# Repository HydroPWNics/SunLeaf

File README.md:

# SunLeaf
SunLeaf is a WiFi based remote sensor module, interfaces with I2C and UART sensors, pushes directly to the cloud.

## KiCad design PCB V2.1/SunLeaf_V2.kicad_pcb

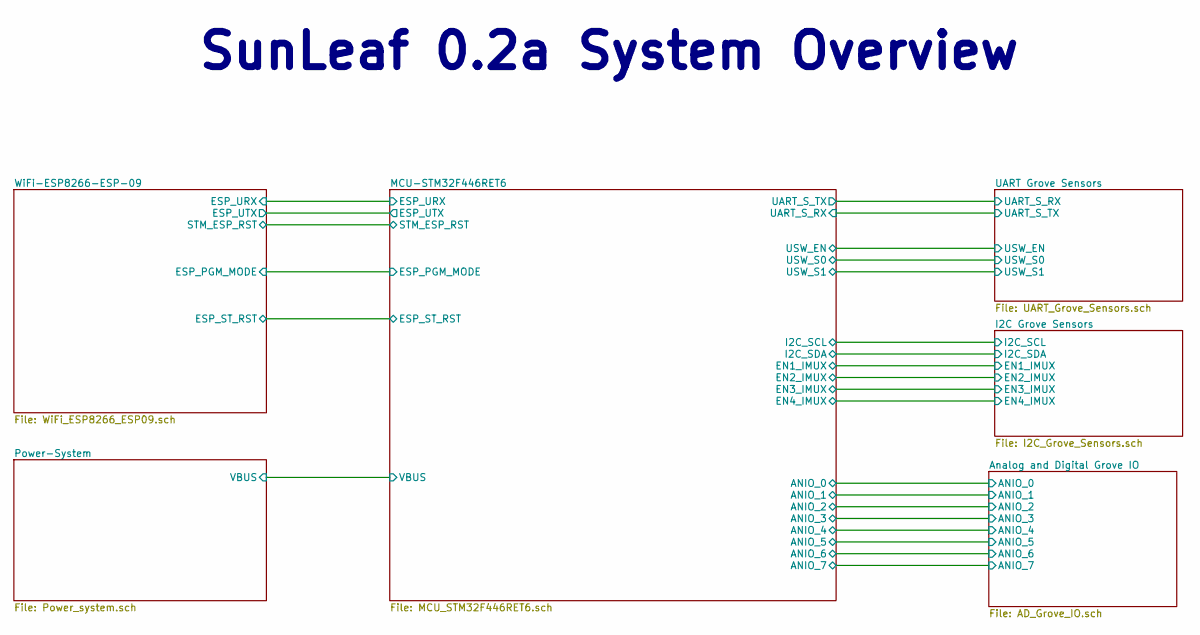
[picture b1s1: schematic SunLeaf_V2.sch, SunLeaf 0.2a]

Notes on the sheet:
SunLeaf 0.2a System Overview

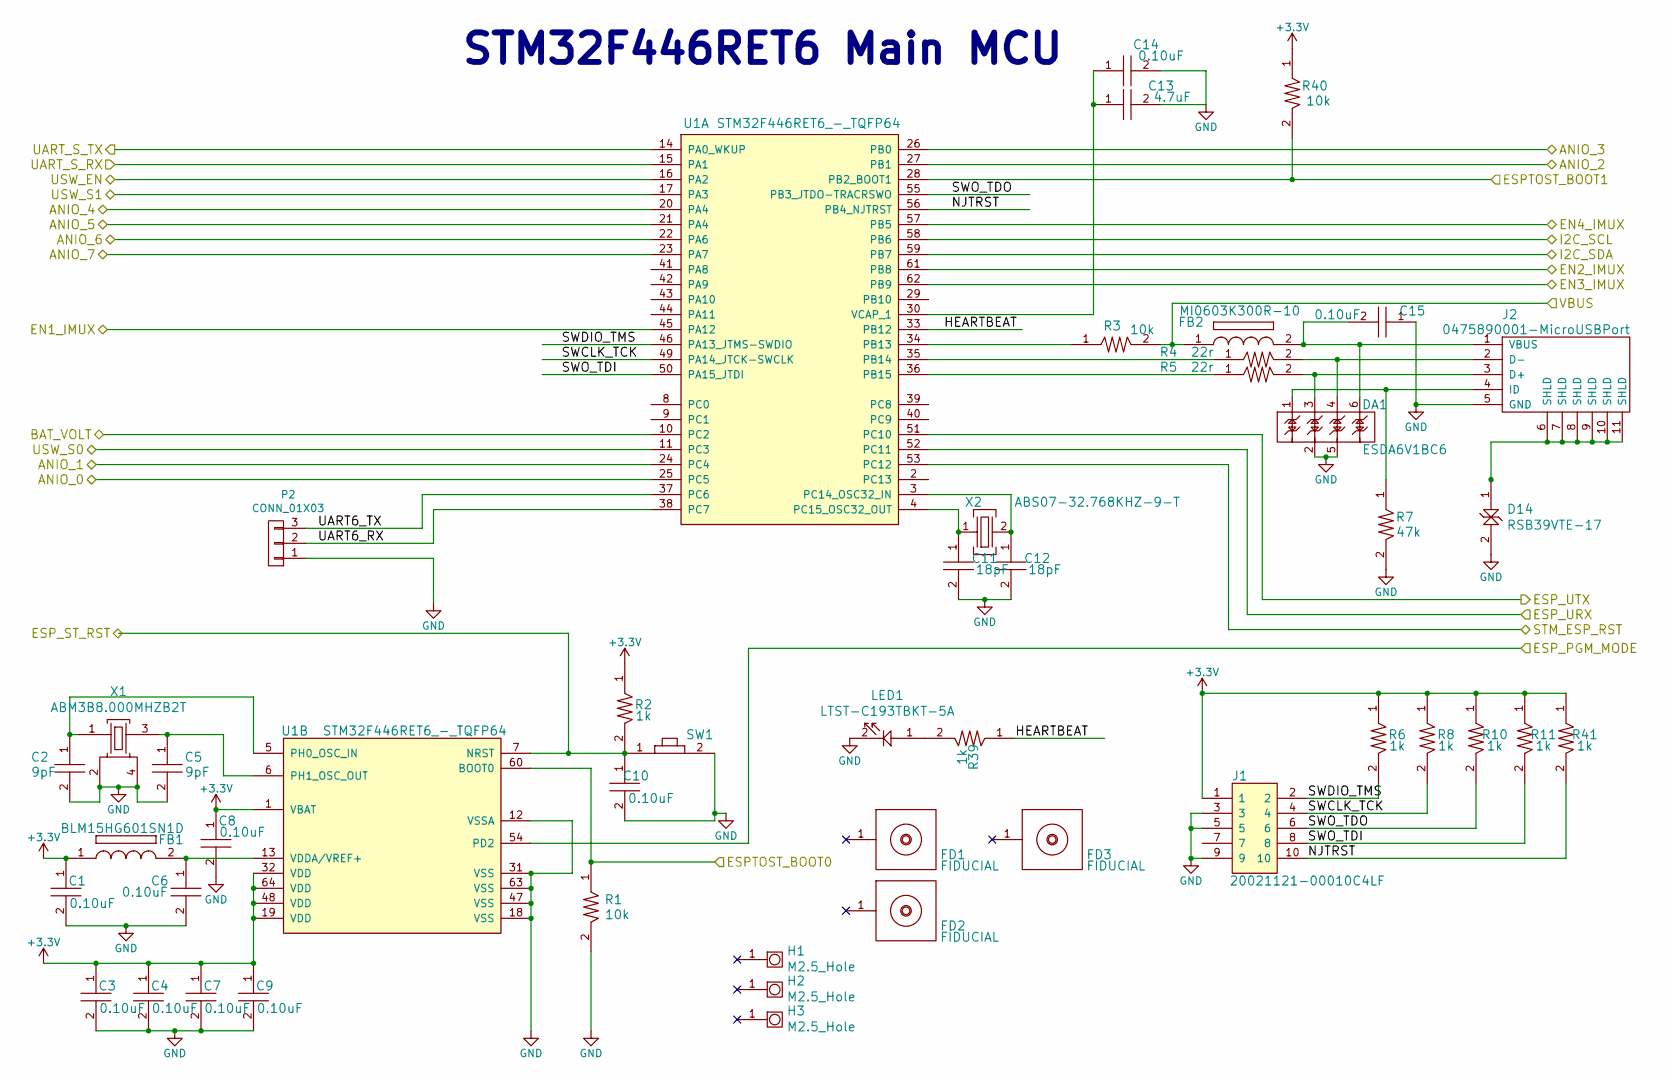
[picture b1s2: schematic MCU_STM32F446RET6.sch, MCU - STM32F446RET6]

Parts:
C1, C3, C4, C6, C7, C8, C9, C10, C14, C15: CL05B104JP5NNNC; C0402; Tolerance 5%; Voltage 10V; MFR# CL05B104JP5NNNC
C2, C5: CL05C090CB5NNNC; C0402; Tolerance 0.25pF; Voltage 50V; MFR# CL05C090CB5NNNC
C11, C12: CL05C180GB5NCNC; C0402; Tolerance 2%; Voltage 50V; MFR# CL05C180GB5NCNC
C13: CL05A475KQ5NRNC; C0402; Tolerance 10%; Voltage 25V; MFR# CL05A475KQ5NRNC
D14: RSB39VTE-17; Tolerance N/A; Voltage 30V; MFR# RSB39VTE-17
DA1: ESDA6V1BC6; Tolerance N/A; Voltage 4V; MFR# ESDA6V1BC6
FB1: BLM15HG601SN1D; Tolerance N/A; Voltage N/A; MFR# BLM15HG601SN1D
FB2: MI0603K300R-10; Tolerance N/A; Voltage N/A; MFR# MI0603K300R-10
FD1, FD2, FD3: FIDUCIAL
H1, H2, H3: M2.5_Hole; M2.5_HOLE
J1: 20021121-00010C4LF; Tolerance N/A; Voltage 200V MAX; MFR# 20021121-00010C4LF
J2: 0475890001-MicroUSBPort; 0475890001; Tolerance N/A; Voltage 5V; MFR# 0475890001
LED1: LTST-C193TBKT-5A; LED0603; Tolerance N/A; Voltage 2.8V Forward Voltage; MFR# LTST-C193TBKT-5A
P2: CONN_01X03; Pin_Header_Straight_1x03
R1, R3, R40: RC1005F103CS; R0402; Tolerance 1%; Voltage N/A; MFR# RC1005F103CS
R2, R6, R8, R10, R11, R39, R41: RC1005F102CS; R0402; Tolerance %; Voltage N/A; MFR# RC1005F102CS
R4, R5: CPF0402B22RE1; R0402; Tolerance 0.1%; Voltage N/A; MFR# CPF0402B22RE1
R7: RC1005J473CS; R0402; Tolerance 5%; Voltage N/A; MFR# RC1005J473CS
SW1: B3U-1000P; Tolerance %; Voltage 50V; MFR# B3U-1000P
U1: STM32F446RET6_-_TQFP64; STM32F446RET6; Tolerance N/A; Voltage 1.8-3.3V; MFR# STM32F446RET6
X1: ABM3B8.000MHZB2T; Tolerance N/A; Voltage 3.3V; MFR# ABM3B-8.000MHZ-B2-T
X2: ABS07-32.768KHZ-9-T; Tolerance ±20ppm; Voltage N/A; MFR# ABS07-32.768KHZ-9-T

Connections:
+3V3: C1.1, C3.1, C4.1, C7.1, C8.1, C9.1, FB1.1, J1.1, R2.1, R6.1, R8.1, R10.1, R11.1, R40.1, R41.1, U1.1 (VBAT), U1.19 (VDD), U1.32 (VDD), U1.48 (VDD), U1.64 (VDD); also elsewhere on the board
/Analog and Digital Grove IO/ANIO_0: U1.25 (PC5); also elsewhere on the board
/Analog and Digital Grove IO/ANIO_1: U1.24 (PC4); also elsewhere on the board
/Analog and Digital Grove IO/ANIO_2: U1.27 (PB1); also elsewhere on the board
/Analog and Digital Grove IO/ANIO_3: U1.26 (PB0); also elsewhere on the board
/Analog and Digital Grove IO/ANIO_4: U1.20 (PA4); also elsewhere on the board
/Analog and Digital Grove IO/ANIO_5: U1.21 (PA4); also elsewhere on the board
/Analog and Digital Grove IO/ANIO_6: U1.22 (PA6); also elsewhere on the board
/Analog and Digital Grove IO/ANIO_7: U1.23 (PA7); also elsewhere on the board
/I2C Grove Sensors/EN1_IMUX: U1.45 (PA12); also elsewhere on the board
/I2C Grove Sensors/EN2_IMUX: U1.61 (PB8); also elsewhere on the board
/I2C Grove Sensors/EN3_IMUX: U1.62 (PB9); also elsewhere on the board
/I2C Grove Sensors/EN4_IMUX: U1.57 (PB5); also elsewhere on the board
/I2C Grove Sensors/I2C_SCL: U1.58 (PB6); also elsewhere on the board
/I2C Grove Sensors/I2C_SDA: U1.59 (PB7); also elsewhere on the board
/MCU-STM32F446RET6/BAT_VOLT: U1.10 (PC2); also elsewhere on the board
/MCU-STM32F446RET6/ESPTOST_BOOT0: R1.1, U1.60 (BOOT0); also elsewhere on the board
/MCU-STM32F446RET6/ESPTOST_BOOT1: R40.2, U1.28 (PB2_BOOT1); also elsewhere on the board
/MCU-STM32F446RET6/ESP_PGM_MODE: U1.54 (PD2); also elsewhere on the board
/MCU-STM32F446RET6/ESP_ST_RST: C10.1, R2.2, SW1.1, U1.7 (NRST); also elsewhere on the board
/MCU-STM32F446RET6/ESP_URX: U1.52 (PC11); also elsewhere on the board
/MCU-STM32F446RET6/ESP_UTX: U1.51 (PC10); also elsewhere on the board
/MCU-STM32F446RET6/HEARTBEAT: R39.1, U1.33 (PB12)
/MCU-STM32F446RET6/NJTRST: J1.10, R41.2, U1.56 (PB4_NJTRST); also elsewhere on the board
/MCU-STM32F446RET6/STM_ESP_RST: U1.53 (PC12); also elsewhere on the board
/MCU-STM32F446RET6/SWCLK_TCK: J1.4, R8.2, U1.49 (PA14_JTCK-SWCLK); also elsewhere on the board
/MCU-STM32F446RET6/SWDIO_TMS: J1.2, R6.2, U1.46 (PA13_JTMS-SWDIO); also elsewhere on the board
/MCU-STM32F446RET6/SWO_TDI: J1.8, R11.2, U1.50 (PA15_JTDI); also elsewhere on the board
/MCU-STM32F446RET6/SWO_TDO: J1.6, R10.2, U1.55 (PB3_JTDO-TRACRSWO); also elsewhere on the board
/MCU-STM32F446RET6/UART6_RX: P2.2, U1.38 (PC7)
/MCU-STM32F446RET6/UART6_TX: P2.3, U1.37 (PC6)
/MCU-STM32F446RET6/UART_S_RX: U1.15 (PA1); also elsewhere on the board
/MCU-STM32F446RET6/USW_EN: U1.17 (PA3); also elsewhere on the board
/MCU-STM32F446RET6/USW_S0: U1.11 (PC3); also elsewhere on the board
/MCU-STM32F446RET6/USW_S1: U1.16 (PA2); also elsewhere on the board
/MCU-STM32F446RET6/VBUS: FB2.1, R3.2; also elsewhere on the board
/UART Grove Sensors/UART_S_RX: U1.14 (PA0_WKUP); also elsewhere on the board
GND: C1.2, C2.2, C3.2, C4.2, C5.2, C6.2, C7.2, C8.2, C9.2, C10.2, C11.2, C12.2, C13.2, C14.2, C15.1, D14.2, DA1.2, DA1.5, J1.3, J1.5, J1.9, J2.5 (GND), LED1.2, P2.1, R1.2, R7.2, SW1.2, U1.12 (VSSA), U1.18 (VSS), U1.31 (VSS), U1.47 (VSS), U1.63 (VSS), X1.2, X1.4; also elsewhere on the board
unnamed: C2.1, U1.5 (PH0_OSC_IN), X1.1
unnamed: C5.1, U1.6 (PH1_OSC_OUT), X1.3
unnamed: C6.1, FB1.2, U1.13 (VDDA/VREF+)
unnamed: C11.1, U1.4 (PC15_OSC32_OUT), X2.1
unnamed: C12.1, U1.3 (PC14_OSC32_IN), X2.2
unnamed: C13.1, C14.1, U1.30 (VCAP_1)
unnamed: C15.2, DA1.6, FB2.2, J2.1 (VBUS)
unnamed: D14.1, J2.6 (SHLD), J2.7 (SHLD), J2.8 (SHLD), J2.9 (SHLD), J2.10 (SHLD), J2.11 (SHLD)
unnamed: DA1.1, J2.4 (ID), R7.1
unnamed: DA1.3, J2.3 (D+), R5.2
unnamed: DA1.4, J2.2 (D-), R4.2
unnamed: LED1.1, R39.2
unnamed 93: R3.1, U1.34 (PB13); also elsewhere on the board
unnamed 94: R4.1, U1.35 (PB14); also elsewhere on the board
unnamed 95: R5.1, U1.36 (PB15); also elsewhere on the board

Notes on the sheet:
STM32F446RET6 Main MCU

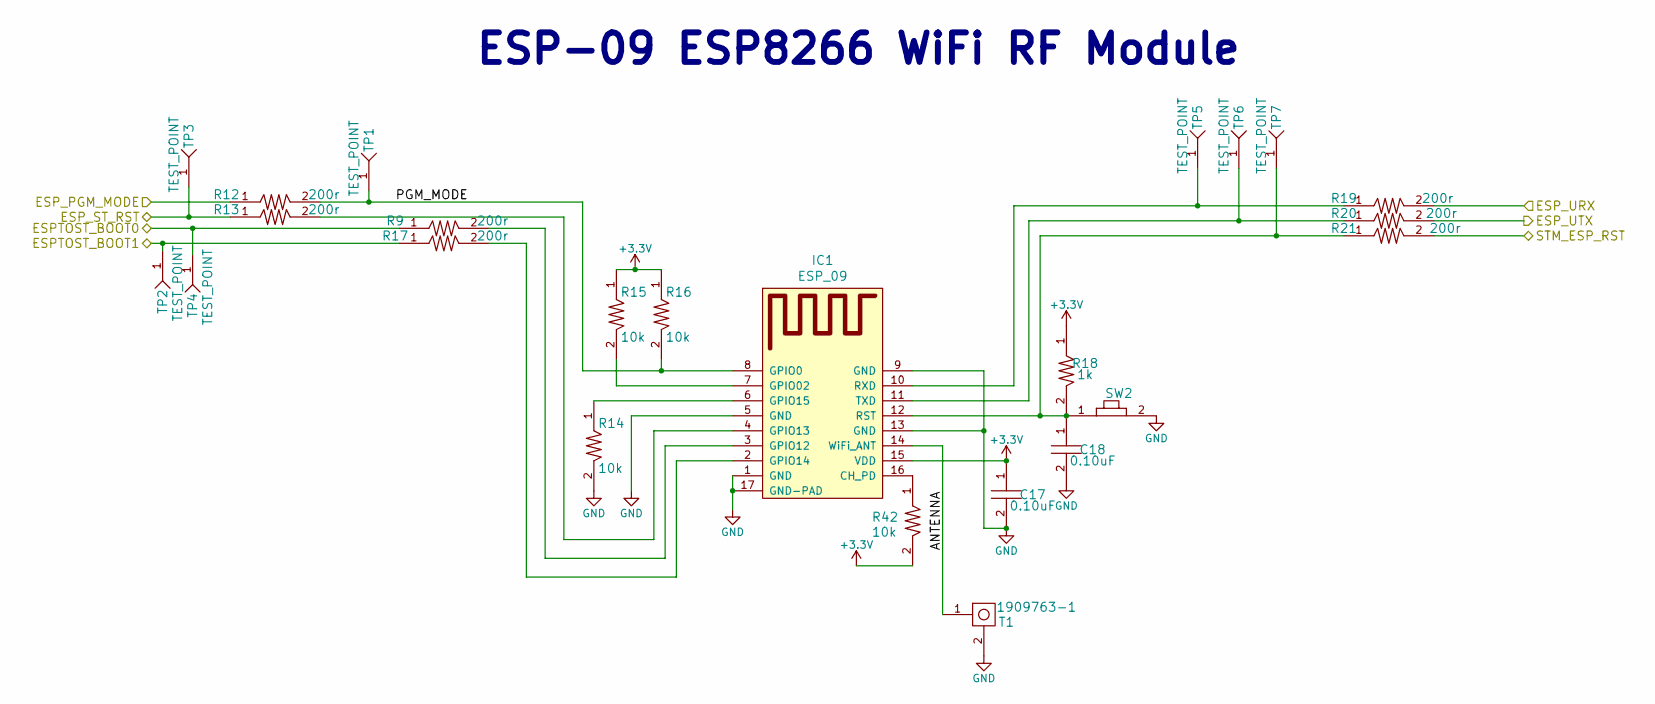
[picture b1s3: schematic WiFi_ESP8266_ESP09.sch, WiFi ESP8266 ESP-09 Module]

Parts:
C17, C18: CL05B104JP5NNNC; C0402; Tolerance 5%; Voltage 10V; MFR# CL05B104JP5NNNC
IC1: ESP_09; ESP-09
R9, R12, R13, R17, R19, R20, R21: RC1005F201CS; R0402; Tolerance 1%; Voltage N/A; MFR# RC1005F201CS
R14, R15, R16, R42: RC1005F103CS; R0402; Tolerance 1%; Voltage N/A; MFR# RC1005F103CS
R18: RC1005F102CS; R0402; Tolerance %; Voltage N/A; MFR# RC1005F102CS
SW2: B3U-1000P; Tolerance %; Voltage 50V; MFR# B3U-1000P
T1: 1909763-1; Tolerance N/A; Voltage N/A; MFR# 1909763-1
TP1, TP2, TP3, TP4, TP5, TP6, TP7: TEST_POINT

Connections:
+3V3: C17.1, IC1.15 (VDD), R15.1, R16.1, R18.1, R42.2; also elsewhere on the board
/MCU-STM32F446RET6/ESPTOST_BOOT0: R9.1, TP4.1; also elsewhere on the board
/MCU-STM32F446RET6/ESPTOST_BOOT1: R17.1, TP2.1; also elsewhere on the board
/MCU-STM32F446RET6/ESP_PGM_MODE: R12.1; also elsewhere on the board
/MCU-STM32F446RET6/ESP_ST_RST: R13.1, TP3.1; also elsewhere on the board
/MCU-STM32F446RET6/ESP_URX: R19.2; also elsewhere on the board
/MCU-STM32F446RET6/ESP_UTX: R20.2; also elsewhere on the board
/MCU-STM32F446RET6/STM_ESP_RST: R21.2; also elsewhere on the board
/WiFi-ESP8266-ESP-09/ANTENNA: IC1.14 (WiFi_ANT), T1.1
/WiFi-ESP8266-ESP-09/PGM_MODE: IC1.8 (GPIO0), R12.2, R16.2, TP1.1
GND: C17.2, C18.2, IC1.1 (GND), IC1.5 (GND), IC1.9 (GND), IC1.13 (GND), IC1.17 (GND-PAD), R14.2, SW2.2, T1.2; also elsewhere on the board
unnamed: C18.1, IC1.12 (RST), R18.2, R21.1, SW2.1, TP7.1
unnamed: IC1.2 (GPIO14), R17.2
unnamed: IC1.3 (GPIO12), R9.2
unnamed: IC1.4 (GPIO13), R13.2
unnamed: IC1.6 (GPIO15), R14.1
unnamed: IC1.7 (GPIO02), R15.2
unnamed: IC1.10 (RXD), R19.1, TP5.1
unnamed: IC1.11 (TXD), R20.1, TP6.1
unnamed: IC1.16 (CH_PD), R42.1

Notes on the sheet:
ESP-09 ESP8266 WiFi RF Module

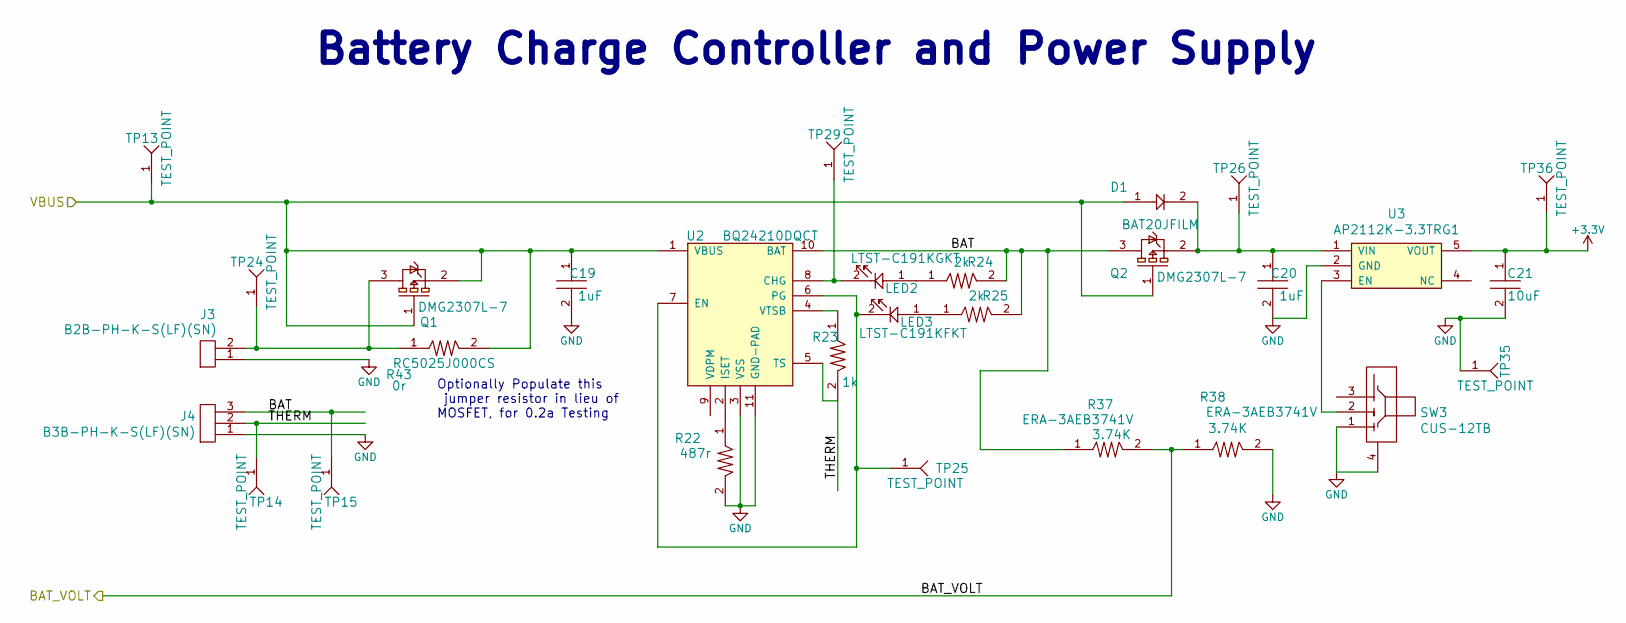
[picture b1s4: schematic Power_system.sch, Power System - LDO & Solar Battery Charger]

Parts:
C19, C20: CL05A105KA5NQNC; C0402; Tolerance 10%; Voltage 25V; MFR# CL05A105KA5NQNC
C21: CL10A106KQ8NNNC; C0603; Tolerance 10%; Voltage 6.3V; MFR# CL10A106KQ8NNNC
D1: BAT20JFILM; Tolerance N/A; Voltage N/A; MFR# BAT20JFILM
J3: B2B-PH-K-S(LF)(SN); Tolerance N/A; Voltage N/A; MFR# B2B-PH-K-S(LF)(SN)
J4: B3B-PH-K-S(LF)(SN); Tolerance N/A; Voltage N/A; MFR# B3B-PH-K-S(LF)(SN)
LED2: LTST-C191KGKT; LED0603; Tolerance N/A; Voltage N/A; MFR# LTST-C191KGKT
LED3: LTST-C191KFKT; LED0603; Tolerance N/A; Voltage N/A; MFR# LTST-C191KFKT
Q1, Q2: DMG2307L-7; Tolerance N/A; Voltage 30V; MFR# DMG2307L-7
R22: RC1005F4870CS; R0402; Tolerance 1%; Voltage N/A; MFR# RC1005F4870CS
R23: RC1005F102CS; R0402; Tolerance %; Voltage N/A; MFR# RC1005F102CS
R24, R25: RC1608J202CS; R0603; Tolerance 1%; Voltage N/A; MFR# RC1608F202CS
R37, R38: ERA-3AEB3741V; R0603; Tolerance 1%; Voltage N/A; MFR# ERA-3AEB3741V
R43: RC5025J000CS; R2010; Tolerance %; Voltage N/A; MFR# RC5025J000CS
SW3: CUS-12TB; Tolerance N/A; Voltage 50V 100mA; MFR# CUS-12TB
TP13, TP14, TP15, TP24, TP25, TP26, TP29, TP35, TP36: TEST_POINT
U2: BQ24210DQCT; BQ24210; Tolerance N/A; Voltage 3.5-18VDC; MFR# BQ24210DQCT
U3: AP2112K-3.3TRG1; Tolerance N/A; Voltage 6V input 3.3V Output; MFR# AP2112K-3.3TRG1

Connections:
+3V3: C21.1, TP36.1, U3.5 (VOUT); also elsewhere on the board
/MCU-STM32F446RET6/BAT_VOLT: R37.2, R38.1; also elsewhere on the board
/MCU-STM32F446RET6/VBUS: C19.1, D1.1, Q1.1, Q1.2, Q2.1, R43.2, TP13.1, U2.1 (VBUS); also elsewhere on the board
/Power-System/BAT: J4.3, Q2.3, R24.2, R25.2, R37.1, TP15.1, U2.10 (BAT)
/Power-System/THERM: J4.2, R23.2, TP14.1, U2.5 (TS)
GND: C19.2, C20.2, C21.2, J3.1, J4.1, R22.2, R38.2, SW3.1, SW3.4, TP35.1, U2.3 (VSS), U2.11 (GND-PAD), U3.2 (GND); also elsewhere on the board
unnamed: C20.1, D1.2, Q2.2, TP26.1, U3.1 (VIN)
unnamed: J3.2, Q1.3, R43.1, TP24.1
unnamed: LED2.1, R24.1
unnamed: LED2.2, TP29.1, U2.8 (CHG)
unnamed: LED3.1, R25.1
unnamed: LED3.2, TP25.1, U2.6 (PG), U2.7 (EN)
unnamed: R22.1, U2.2 (ISET)
unnamed: R23.1, U2.4 (VTSB)
unnamed: SW3.2, U3.3 (EN)

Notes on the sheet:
Battery Charge Controller and Power Supply
Optionally Populate this jumper resistor in lieu of MOSFET, for 0.2a Testing

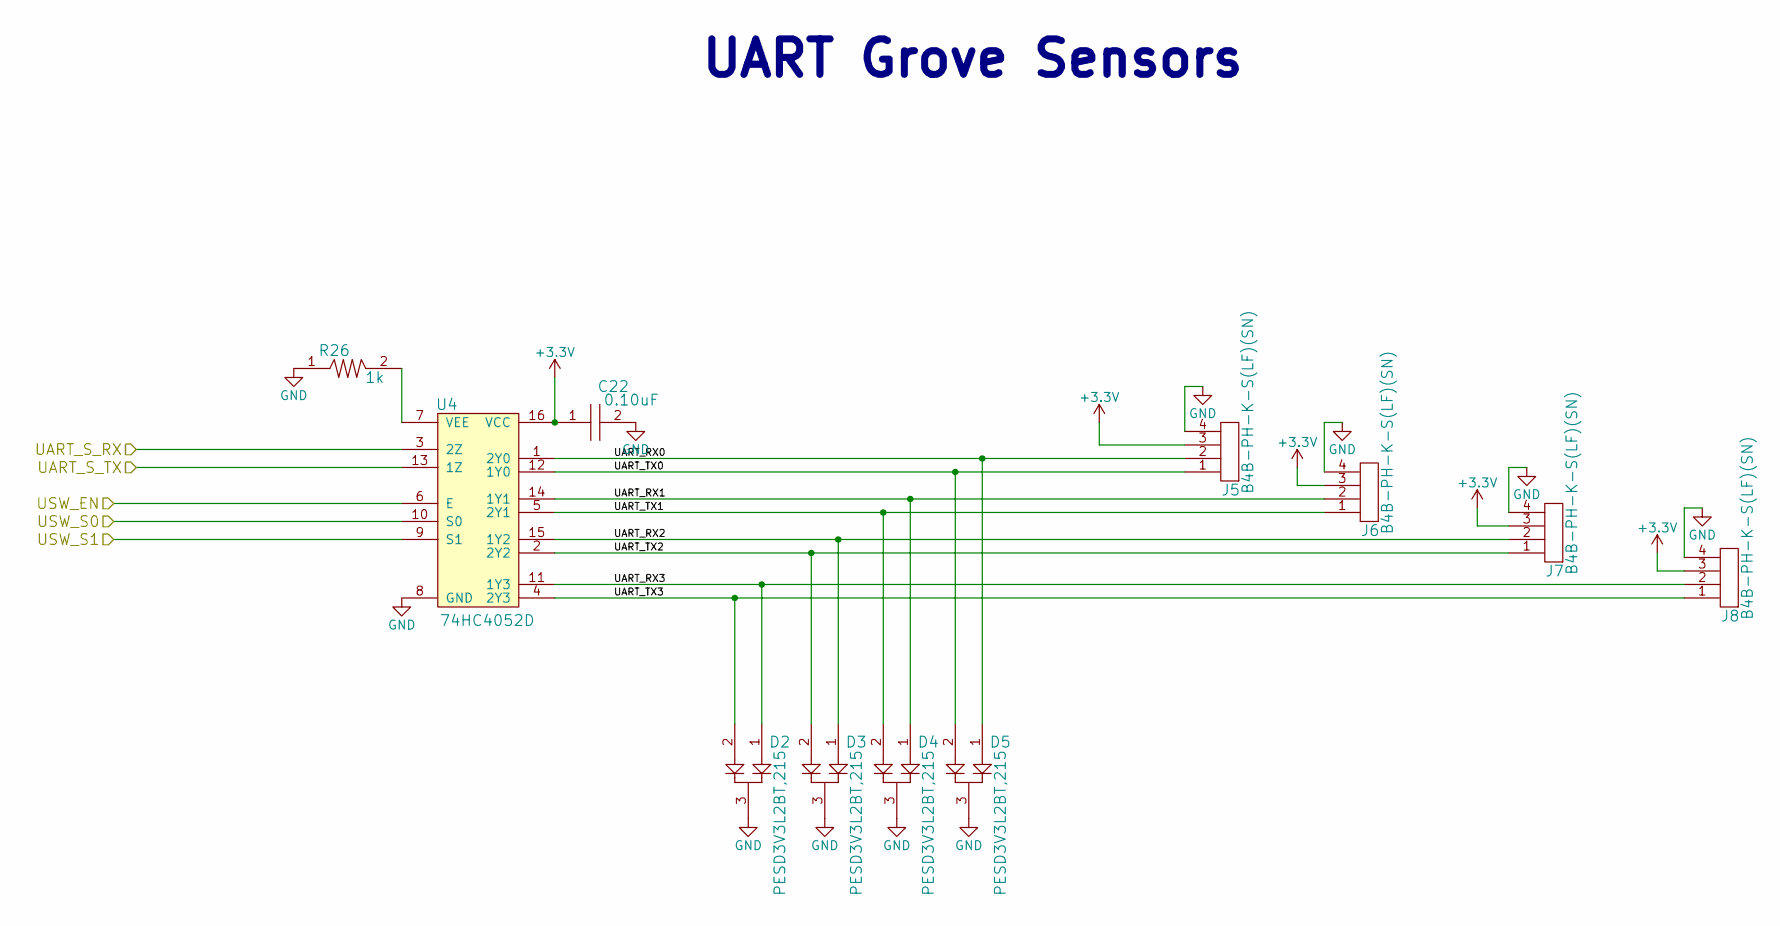
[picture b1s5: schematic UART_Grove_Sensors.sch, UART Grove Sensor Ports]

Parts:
C22: CL05B104JP5NNNC; C0402; Tolerance 5%; Voltage 10V; MFR# CL05B104JP5NNNC
D2, D3, D4, D5: PESD3V3L2BT,215; Tolerance N/A; Voltage N/A; MFR# PESD3V3L2BT,215
J5, J6, J7, J8: B4B-PH-K-S(LF)(SN); Tolerance N/A; Voltage N/A; MFR# B4B-PH-K-S(LF)(SN)
R26: RC1005F102CS; R0402; Tolerance %; Voltage N/A; MFR# RC1005F102CS
U4: 74HC4052D; Tolerance N/A; Voltage 3.3V; MFR# 74HC4052D,653

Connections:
+3V3: C22.1, J5.3, J6.3, J7.3, J8.3, U4.16 (VCC); also elsewhere on the board
/MCU-STM32F446RET6/UART_S_RX: U4.13 (1Z); also elsewhere on the board
/MCU-STM32F446RET6/USW_EN: U4.6 (E); also elsewhere on the board
/MCU-STM32F446RET6/USW_S0: U4.10 (S0); also elsewhere on the board
/MCU-STM32F446RET6/USW_S1: U4.9 (S1); also elsewhere on the board
/UART Grove Sensors/UART_RX0: D5.1, J5.2, U4.1 (2Y0)
/UART Grove Sensors/UART_RX1: D4.1, J6.2, U4.14 (1Y1)
/UART Grove Sensors/UART_RX2: D3.1, J7.2, U4.15 (1Y2)
/UART Grove Sensors/UART_RX3: D2.1, J8.2, U4.11 (1Y3)
/UART Grove Sensors/UART_S_RX: U4.3 (2Z); also elsewhere on the board
/UART Grove Sensors/UART_TX0: D5.2, J5.1, U4.12 (1Y0)
/UART Grove Sensors/UART_TX1: D4.2, J6.1, U4.5 (2Y1)
/UART Grove Sensors/UART_TX2: D3.2, J7.1, U4.2 (2Y2)
/UART Grove Sensors/UART_TX3: D2.2, J8.1, U4.4 (2Y3)
GND: C22.2, D2.3, D3.3, D4.3, D5.3, J5.4, J6.4, J7.4, J8.4, R26.1, U4.8 (GND); also elsewhere on the board
unnamed: R26.2, U4.7 (VEE)

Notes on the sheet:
UART Grove Sensors

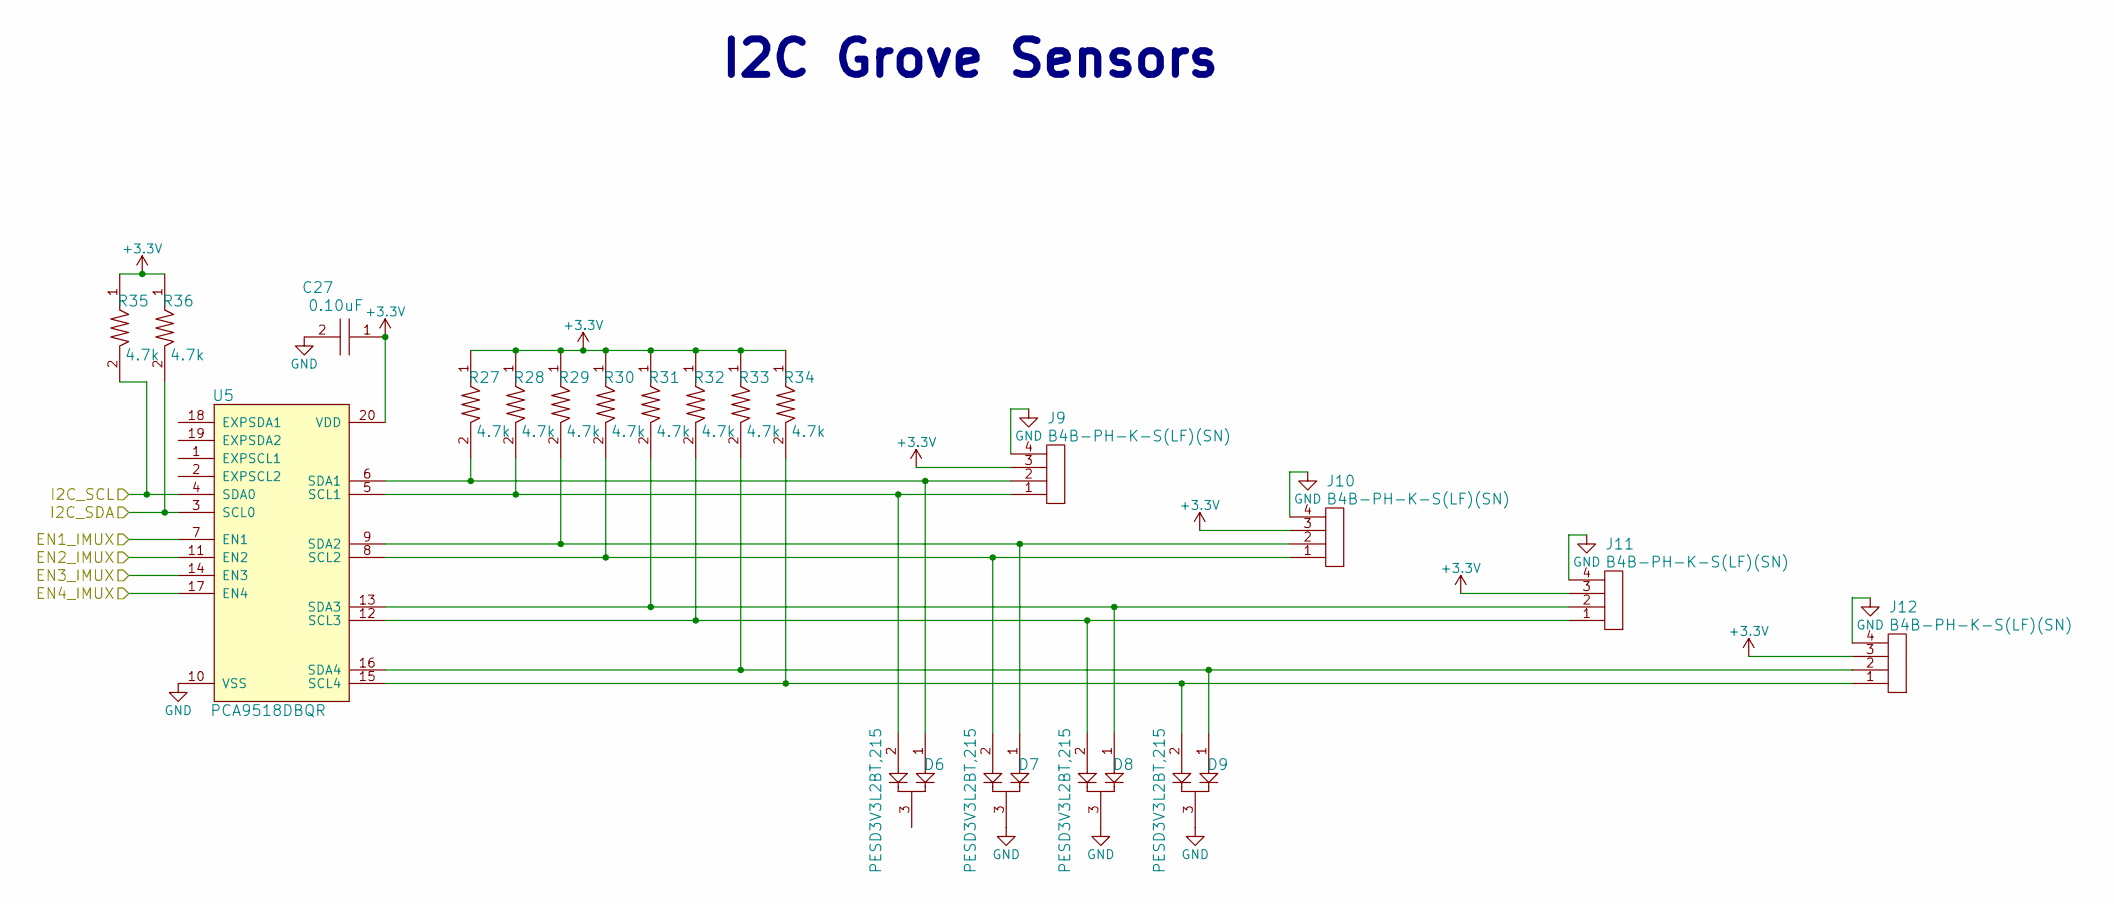
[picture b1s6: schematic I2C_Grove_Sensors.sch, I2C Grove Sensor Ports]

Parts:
C27: CL05B104JP5NNNC; C0402; Tolerance 5%; Voltage 10V; MFR# CL05B104JP5NNNC
D6, D7, D8, D9: PESD3V3L2BT,215; Tolerance N/A; Voltage N/A; MFR# PESD3V3L2BT,215
J9, J10, J11, J12: B4B-PH-K-S(LF)(SN); Tolerance N/A; Voltage N/A; MFR# B4B-PH-K-S(LF)(SN)
R27, R28, R29, R30, R31, R32, R33, R34, R35, R36: RC1005F472CS; R0402; Tolerance 1%; Voltage N/A; MFR# RC1005F472CS
U5: PCA9518DBQR; Tolerance N/A; Voltage 3.3V; MFR# PCA9518DBQR

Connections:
+3V3: C27.1, J9.3, J10.3, J11.3, J12.3, R27.1, R28.1, R29.1, R30.1, R31.1, R32.1, R33.1, R34.1, R35.1, R36.1, U5.20 (VDD); also elsewhere on the board
/I2C Grove Sensors/EN1_IMUX: U5.7 (EN1); also elsewhere on the board
/I2C Grove Sensors/EN2_IMUX: U5.11 (EN2); also elsewhere on the board
/I2C Grove Sensors/EN3_IMUX: U5.14 (EN3); also elsewhere on the board
/I2C Grove Sensors/EN4_IMUX: U5.17 (EN4); also elsewhere on the board
/I2C Grove Sensors/I2C_SCL: R35.2, U5.4 (SDA0); also elsewhere on the board
/I2C Grove Sensors/I2C_SDA: R36.2, U5.3 (SCL0); also elsewhere on the board
GND: C27.2, D7.3, D8.3, D9.3, J9.4, J10.4, J11.4, J12.4, U5.10 (VSS); also elsewhere on the board
unnamed: D6.1, J9.2, R27.2, U5.6 (SDA1)
unnamed: D6.2, J9.1, R28.2, U5.5 (SCL1)
unnamed: D7.1, J10.2, R29.2, U5.9 (SDA2)
unnamed: D7.2, J10.1, R30.2, U5.8 (SCL2)
unnamed: D8.1, J11.2, R31.2, U5.13 (SDA3)
unnamed: D8.2, J11.1, R32.2, U5.12 (SCL3)
unnamed: D9.1, J12.2, R33.2, U5.16 (SDA4)
unnamed: D9.2, J12.1, R34.2, U5.15 (SCL4)

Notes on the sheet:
I2C Grove Sensors

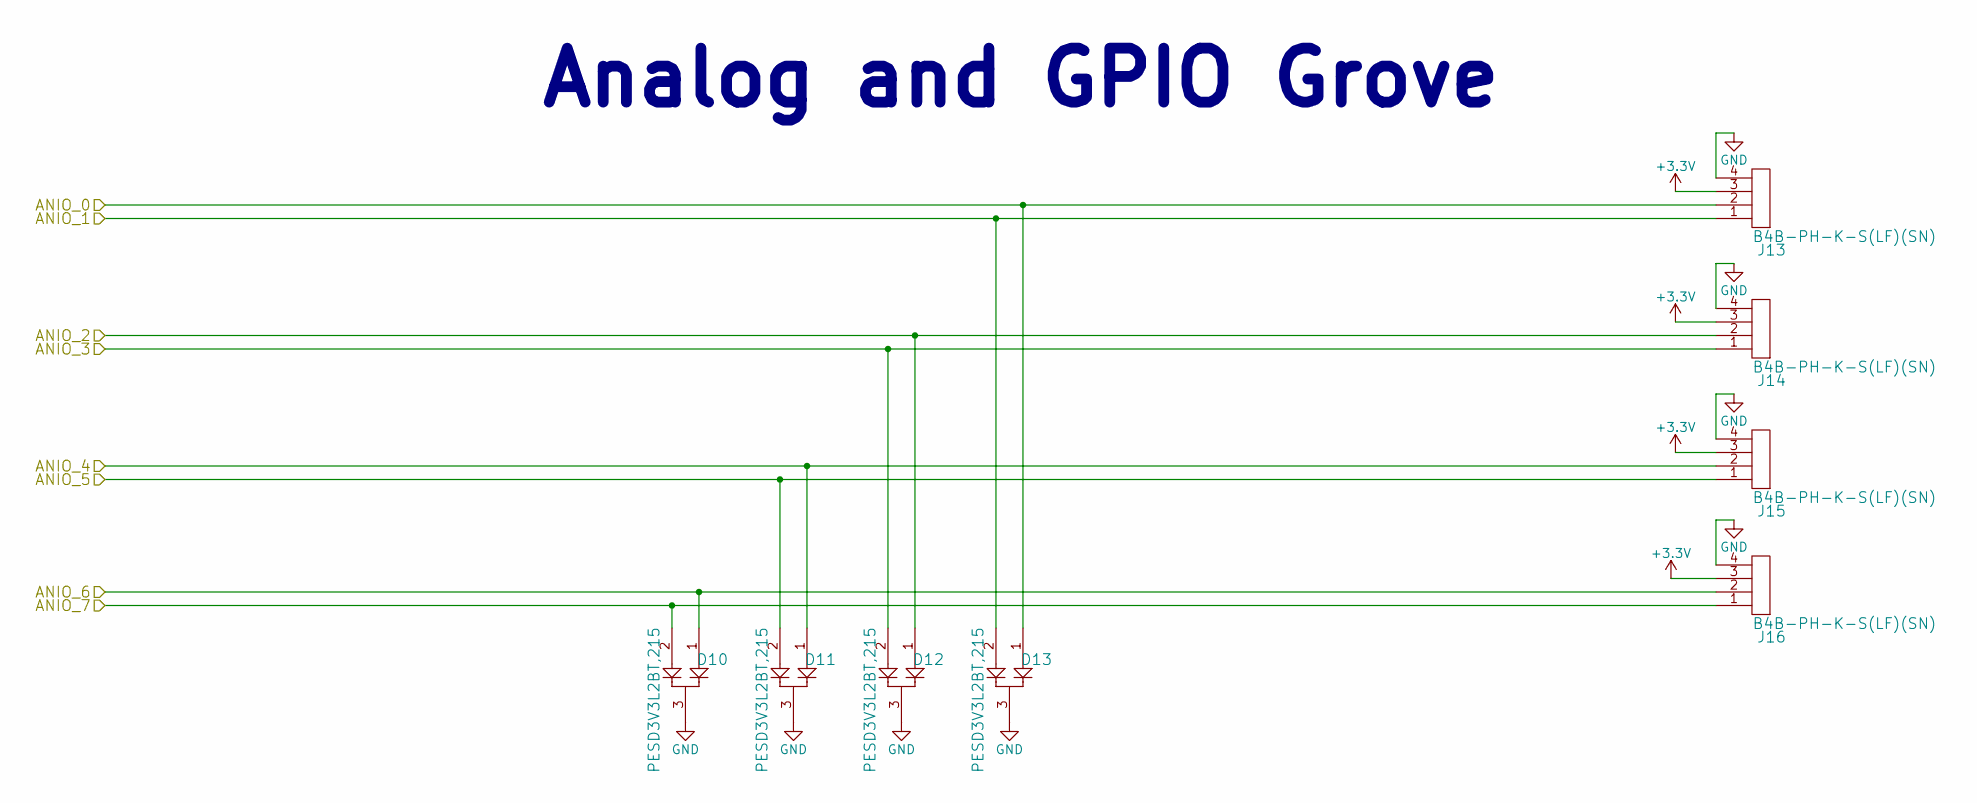
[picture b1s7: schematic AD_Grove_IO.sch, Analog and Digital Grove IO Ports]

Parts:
D10, D11, D12, D13: PESD3V3L2BT,215; Tolerance N/A; Voltage N/A; MFR# PESD3V3L2BT,215
J13, J14, J15, J16: B4B-PH-K-S(LF)(SN); Tolerance N/A; Voltage N/A; MFR# B4B-PH-K-S(LF)(SN)

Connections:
+3V3: J13.3, J14.3, J15.3, J16.3; also elsewhere on the board
/Analog and Digital Grove IO/ANIO_0: D13.1, J13.2; also elsewhere on the board
/Analog and Digital Grove IO/ANIO_1: D13.2, J13.1; also elsewhere on the board
/Analog and Digital Grove IO/ANIO_2: D12.1, J14.2; also elsewhere on the board
/Analog and Digital Grove IO/ANIO_3: D12.2, J14.1; also elsewhere on the board
/Analog and Digital Grove IO/ANIO_4: D11.1, J15.2; also elsewhere on the board
/Analog and Digital Grove IO/ANIO_5: D11.2, J15.1; also elsewhere on the board
/Analog and Digital Grove IO/ANIO_6: D10.1, J16.2; also elsewhere on the board
/Analog and Digital Grove IO/ANIO_7: D10.2, J16.1; also elsewhere on the board
GND: D10.3, D11.3, D12.3, D13.3, J13.4, J14.4, J15.4, J16.4; also elsewhere on the board

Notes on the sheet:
Analog and GPIO Grove

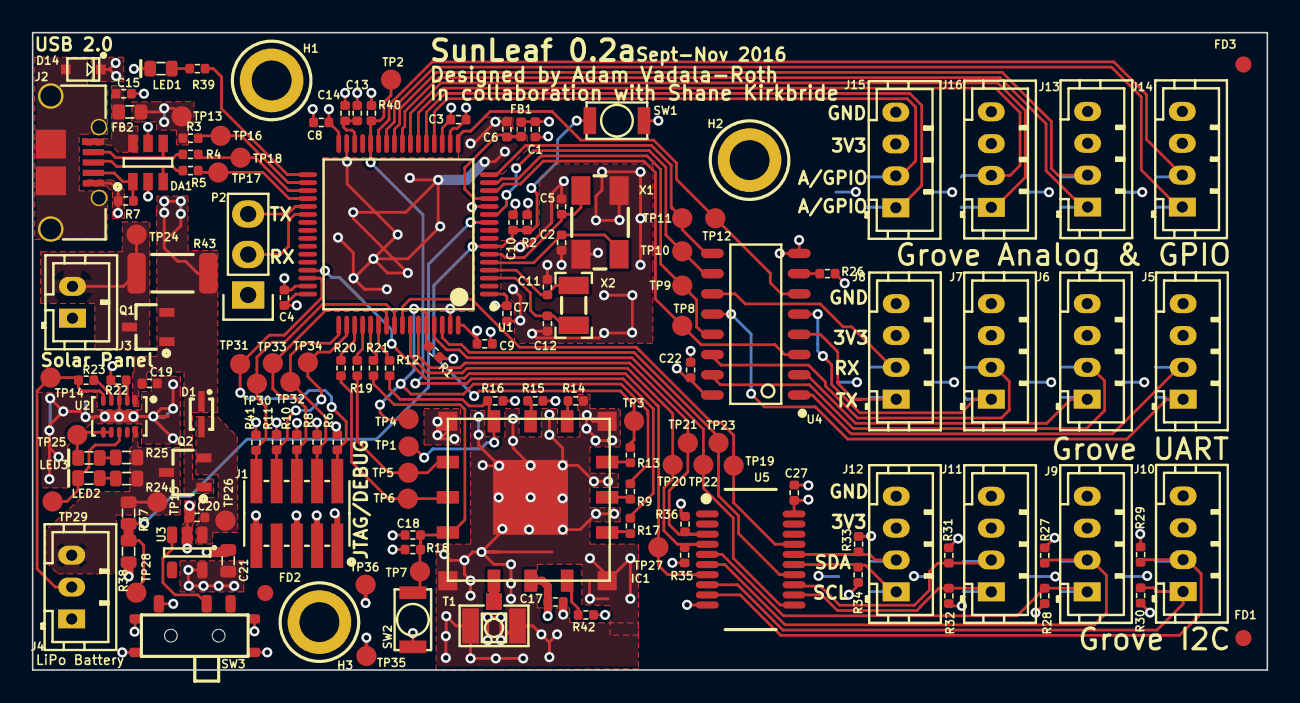
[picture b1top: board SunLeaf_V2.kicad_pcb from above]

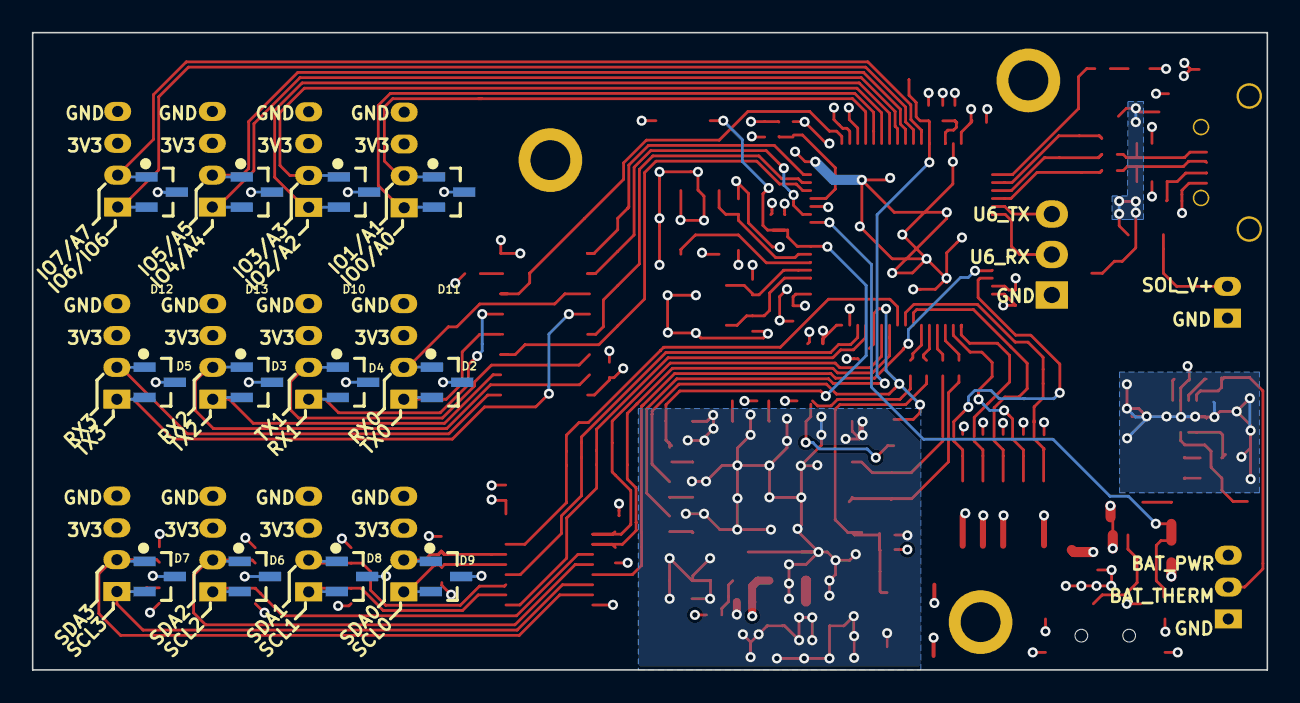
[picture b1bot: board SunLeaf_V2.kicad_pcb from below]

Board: 4 copper layers, 77.5 x 40.0 mm, 158 parts (12 on the bottom side), 92 nets.

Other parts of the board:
TP8, TP9, TP10, TP11, TP12, TP16, TP17, TP18, TP19, TP20, TP21, TP22, TP23, TP27, TP28, TP30, TP31, TP32, TP33, TP34: TEST_POINT

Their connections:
/I2C Grove Sensors/EN1_IMUX: TP27.1; also elsewhere on the board
/I2C Grove Sensors/EN2_IMUX: TP22.1; also elsewhere on the board
/I2C Grove Sensors/EN3_IMUX: TP23.1; also elsewhere on the board
/I2C Grove Sensors/EN4_IMUX: TP19.1; also elsewhere on the board
/I2C Grove Sensors/I2C_SCL: TP20.1; also elsewhere on the board
/I2C Grove Sensors/I2C_SDA: TP21.1; also elsewhere on the board
/MCU-STM32F446RET6/BAT_VOLT: TP28.1; also elsewhere on the board
/MCU-STM32F446RET6/NJTRST: TP30.1; also elsewhere on the board
/MCU-STM32F446RET6/SWCLK_TCK: TP32.1; also elsewhere on the board
/MCU-STM32F446RET6/SWDIO_TMS: TP31.1; also elsewhere on the board
/MCU-STM32F446RET6/SWO_TDI: TP34.1; also elsewhere on the board
/MCU-STM32F446RET6/SWO_TDO: TP33.1; also elsewhere on the board
/MCU-STM32F446RET6/UART_S_RX: TP9.1; also elsewhere on the board
/MCU-STM32F446RET6/USW_EN: TP12.1; also elsewhere on the board
/MCU-STM32F446RET6/USW_S0: TP10.1; also elsewhere on the board
/MCU-STM32F446RET6/USW_S1: TP11.1; also elsewhere on the board
/UART Grove Sensors/UART_S_RX: TP8.1; also elsewhere on the board
unnamed 93: TP16.1; also elsewhere on the board
unnamed 94: TP18.1; also elsewhere on the board
unnamed 95: TP17.1; also elsewhere on the board

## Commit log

2016-03-31 Footprints and Schematic
    Preliminary footprint creation for new MCU completed. Schematic nearly
    finished currently working on the STM32 section all others are done save
    for some ESD supression on the sensor connectors.
2016-04-03 Schematic Near COmplete
    All left is connecting subsystems to STM32F4 and finishign the USB
    circuit.
2016-04-07 Schematic Finished Board Started
    Schematic complete but subject to change and PCB started.
2016-04-08 PCB Progress
    More progress on PCB, bottom mounting all ESD components on grove
    sensors.
2016-04-11 Board Progress
    Board progressing along, schematic for I2C and UART connectors pin
    swapped for correct pinout.
2016-04-27 Board
    Lots of progress with the PCB, size increased to 1.25 X 3.5 inches to
    better fit circuitry and allow for an adequate keep out layer. Expansion
    connectors are being added but highly subject to change a few times
    before finalizing. The ESP-02 module's UART signals are jumperable to
    connect it to either the STM32 or a programming pin header. Discussing
    with Shane about further improvements and ESD suppression.
2016-04-29 Nearing COmpletion
    Added graphics for designer credit, hackaday prize, and open hardware.
    Still working out expansion headers.
2016-05-02 Done
    Board finished, awaiting discussion with Shane
2016-05-05 Board CHanges
    Shielding copper pour tied to ground for the ESP-02 module added.
    Routing adjusted and cleaned up. Alligator clip test point added for
    scope probe grounding.
2016-05-06 Test Points and Cleanup
    Errors cleaned up (unrouted nets etc), test points added. More to
    follow.
2016-05-09 Schematic Review and Change
    Shematic went under futher review, additional cap added to VCAP pin and
    other pins tied GND instead of though caps, misunderstanding of the
    Nucleo schematic vs. datasheet spec.
2016-05-24 Design Finished and Off To Fab
    Design now frozen in place for prototype 1 fabrication, assembly and
    test. The libraries saw a massive cleanup, the USB section redesigned
    with the correct signal order! 3D step file included, and OSHPark order
    files.
2016-06-05 3D Fixes
    Component with incorrect Z axis offset, fixed and 3D model accurately
    regenerated.
2016-08-08 Nucleo-STLink
    fully completed project for a PCB adapter for the ST Nucleo board's
    programming header. adapts the 6 pin SWD header to a ARM Cortex M debug
    header.
2016-08-22 V2 begun
    Version 2 and KiCAD port started
2016-09-09 SunLeaf Alpha 0.2 and KiCAD Port
    SunLeaf rev 2 called Alhpa 0.2 or 0.2a is the main component of this
    commit. The entire hardware project has been ported to KiCAD libaries
    and all. 0.2a features a revised formfactor, better ESP module, and many
    fixes over the original. This version will also be capable of OTA
    updates.
2016-09-09 Update
    Updating KiCAD to the latest to get rounded corner pad support, filing
    this commit as a backup of the project before update.
2016-09-17 Placement
    Heavy progress on component placement in KiCAD for SunLEaf V2,
    committing to save progress, nightly builds of KiCAD are very crash
    prone.
2016-09-17 Placement near completeq
    placement is near complete, saving as revision, remember KiCAD=crash
2016-09-17 Revert "Placement near completeq"
    This reverts commit ae7bce2a0b52adb9ec10d03d9117548a28df5835.
2016-09-17 Placement progress
    Placement is 99% done board is being resized. Next commit TVS diode
    pairs will be fliped and the baord further resized.
2016-09-17 Routing and Placement
    Placement complete routing has begun. The board size has also been
    solidified.
2016-09-17 Routing Progress
    Routing progress made, UART and I2C sensors routed, ESP routed, power
    section and solar batter routed, USB routed.
2016-09-17 Route 99%
    PCB routing at 99%, next commit complete route and internal layers.
2016-09-17 Internal Planes
    Internal Planes added, small amount of routing left.
2016-09-17 PDF
    Schematic PDF updated.
2016-09-18 Workstation Switch
    Switching to laptop, syncing files.
2016-09-19 OTA
    This commit contains adjustments to the schematics for over the air
    update/programming of STM32 via the ESP8266 using its internal
    bootloader. The two processors have been wired together to suppor this
    fucntions, they can toggle reset of eachother and load firmware over
    UART. Still deciding what reset signal pin on the STM32 to use fo rthis
    purpose, next commit.
2016-09-19 Battery Monitoring & OTA
    OTA signals between both processors solidified and routed. Battery
    monitoring added as voltage divider into ADC channel. All but done
    pending some small tweaks.
2016-09-21 App Notes
    App notes added to datasheets folder.
2016-09-23 DRC Clearing
    More DRC errors cleared. Getting board ready for fab.
2016-09-26 DRC clear
    all design rule violations cleared.
2016-09-29 3D and Tweaks
    3D files added for components for proper 3D rneder of the board. Board
    tweaked, additional ground pours and sticking under neath the ESP-09,
    cleaned up routign of JTAG , added labeling of all the pin signals.
2016-09-29 License
    CERN Open Hardware License Added
2016-09-29 Repo Cleanup
    Repo cleaned up and braought up to date
2016-09-29 Schematic Changes
    Schematic changes saved.
2016-10-04 Test Points
    Test points added as well as some retooling of the PCB overall. More
    updates to come before the pending fab
2016-10-04 Updated PDF
    Updated PDF of schematic indluding the newly added test points!
2016-10-05 JTAG Test Points
    Test Points added to JTAG.
2016-10-05 Images
    Images added and organized
2016-10-30 LDO and Switch
    LDO swapped out for one that better matches the complete system's
    amperage requirements. The LDO is now a 600mA one and has a toggle
    switch for shuttingit on and off, this will allow the SunLeaf to be
    stored and or shipped.
2016-11-01 Diode Error
    The pin numbering on the footprint for the diode in the LDO input source
    switching circiut was revered, it has now been adjusted to be correct.
